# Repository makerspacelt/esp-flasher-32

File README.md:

This is ESP-WROOM-32 interface to connect with the [esp-flasher](http://esp-flasher.makerspace.lt/repo), featuring pogo-pin snap-on design.

* Designed to snap on top of any ESP-WROOM-32 module without any provisions for programming or debugging in-place

Support this open-source project - buy your fully assembled and tested device [here](http://esp-32.makerspace.lt/shop)

Dev NOTE: before commit, run `./kibot.sh` to regenerate documentation, gerbers and other assets.

* [schematics.pdf](gen/schematics.pdf)
* [pcb.pdf with dimensions](gen/pcb.pdf)

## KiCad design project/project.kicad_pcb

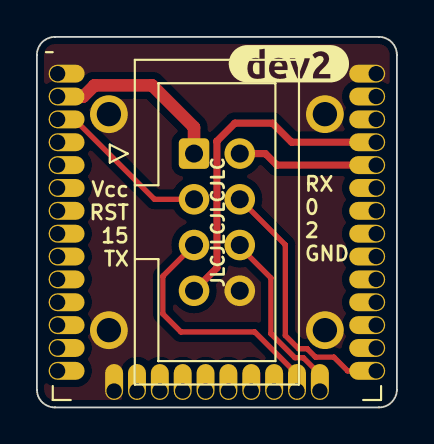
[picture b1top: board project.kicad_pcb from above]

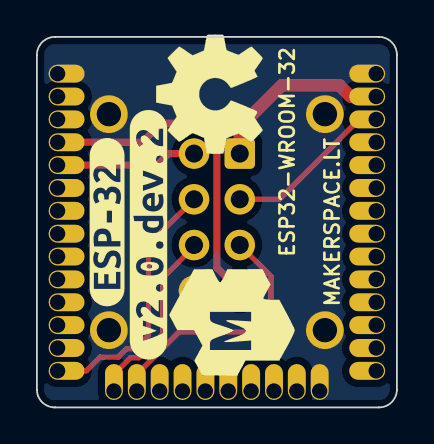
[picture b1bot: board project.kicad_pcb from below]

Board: 2 copper layers, 20.0 x 20.6 mm, 11 parts (4 on the bottom side), 8 nets.

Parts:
G1: Logo_Open_Hardware_Large; OSHW-Symbol_6.7x6mm_SilkScreen
G2: LOGO_KMS; logo_kms_small_silkscreen
H1, H2, H3, H4: MountingHole_Pad; MountingHole_1.35mm_M1.2_Pad
J1: flasher; IDC-Header_2x04_P2.54mm_Vertical
U1: ESP32-WROOM-32
kibuzzard-64DF4388: G***; kibuzzard-64DF4388
kibuzzard-64E4955A: G***; kibuzzard-64E4955A
kibuzzard-64E49519: G***; kibuzzard-64E49519

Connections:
EN: J1.5, U1.23 (IO15)
GND: H1.1, H2.1, H3.1, H4.1, J1.8, U1.1 (GND), U1.15 (GND), U1.38 (GND)
IO0: J1.4, U1.25 (IO0)
IO2: J1.6, U1.24 (IO2)
RST: J1.3, U1.3 (EN)
RX: J1.2, U1.34 (RXD0/IO3)
TX: J1.7, U1.35 (TXD0/IO1)
Vcc: J1.1, U1.2 (VDD)

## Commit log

2023-08-01 adding esp32 pogo pin pcb
2023-08-06 marking version
2023-08-18 using smaller 2x4 connector and shrinking pcb
2023-08-22 adding 4 screwholes for mounting
2023-08-22 added jlc silkscreen text
